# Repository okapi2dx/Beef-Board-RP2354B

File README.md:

# Beef Board RP2354B

Beef Board RP2354B の基板設計、ファームウェア、Windows 用 Configurator をまとめたプロジェクトです。Configurator は、RP2354B と従来の AT90USB1286 の2種類のマイコンを搭載した基板に対応します。

## 開発とソースコードの由来

基板、ファームウェア、Configurator の設計・実装・デバッグ・文書作成に AI を活用しています。仕様と設計の採用判断はプロジェクト管理者が行います。実機での確認状況は各ファームウェアの README に記載しています。

Configurator は [HWXLR8/beef-board](https://github.com/HWXLR8/beef-board) を基にした Beef Board ソフトウェアのフォーク／派生コードを出発点として、RP2354B 対応を加えています。

## Configurator

RP2354B・AT90USB1286に対応するWindowsアプリです。入力、LED、キー割り当てを設定し、モニターと波形で動作を確認できます。

[V1.00リリース](https://github.com/okapi2dx/Beef-Board-RP2354B/releases/tag/V1.00)から最新のアプリと基板用ファームを取得し、USB接続後に **「接続」** を押してください。設定は基板へ自動反映され、各項目の **「?」** で説明を確認できます。

以下は現在のアプリを日本語・ダークモードで表示した例です。画像内の入力・数値は説明用のサンプルです。

### 入力設定

入力モードを **ジョイスティック / キーボード** から選び、ターンテーブルの回転方向やアナログ / デジタル入力を設定します。下部の **X軸** で回転による入力を確認できます。

- **デッドゾーン：0～50カウント。** 小さな回転を無視する範囲です。0で無効になります。
- **感度：0.000～2.000。** 1.000が基準、0.500で半分、2.000で2倍の距離を進みます。0で入力無効、初期値は1.000です。
- **保持時間：** デジタル入力が途切れる場合に調整します。アナログ入力にはジョイスティックモードを使用してください。

### LED・RGB設定

**「ボタンLED設定」** では、ボタンの明るさ・フェードアウト時間・点灯反転を調整します。**「RGB LED設定」** では、ターンテーブルとセンターバーの色・発光効果を設定します。

- **連動：** ターンテーブルとセンターバーを同じ色・発光効果にできます。
- **変化速度：** 回転・シフト・動くレインボー・呼吸の速度を1～5で調整します。自動で色が変わる効果では、色選択がグレーアウトします。
- **LED数：** 接続したLED数に合わせて各0～255で設定します。初期値はターンテーブル24個、センターバー16個。0でそのLED出力を無効にします。
- **旧PHOENIXWAN：** RP2354BではUART接続によるLED制御に対応します。

| ボタンLED設定 | RGB LED設定 |
|---|---|
|  |  |

### コントローラーモニター

ボタンの入力、X軸、割り当て先とLEDの光り方を確認できます。**1P / 2P** で配置を切り替え、デジタル入力では回転方向を **B13 / B14** の点灯で表示します。

### チャタリングテスト

**B1～B7の波形と入力ログ** を見ながら、押下時・解放時の抑制を各 **0.0～16.0ms** で調整できます。一括設定と自動設定にも対応します。

**「抑制前 / 抑制後」** で、元の入力と現在の設定を適用した波形を比較します。ログを選んで **「詳細」** を押すと、そのボタンの50ms区間を拡大します。2つのエッジを選ぶと、間の押下・解放時間を測定できます。

### キー割り当て・ファームウェア更新

**「キー割り当て」** で、ボタンの割り当て先やキーボード入力のキーを変更できます。**「ファームウェア」** から更新方法を確認してください。AT90USB1286はHEXをアプリから書き込み、RP2354BはUF2をBOOTSELのUSBドライブへコピーします。

ライト / ダークと日本語 / Englishを切り替えられます。詳しい手順は [ConfiguratorのREADME](configurator/README.md)、[ファームウェアのREADME](firmware/README.md) を参照してください。

## 旧PHOENIXWAN UART

RP2354B基板のUART端子は、**旧PHOENIXWANのターンテーブルリングとセンターバーLEDを接続して制御する用途**です。ターンテーブルリングはJ42、センターバーはJ43に接続し、ConfiguratorのLED設定に合わせて制御します。このUART機能はAT90USB1286基板にはありません。

UARTプロトコルで設定できる色や発光パターンには制限があります。対応する制御内容と接続上の注意は [`firmware/README.md`](firmware/README.md) を参照してください。旧PHOENIXWAN実機での接続確認は未実施です。

## 電源選択（J2）

J2「POWER SELECT」のショート位置で、USBケーブル1本または2本の使い方を選べます。

| 使い方 | J2の設定 | 接続方法 |
|---|---|---|
| USBケーブル1本 | 1–2を短絡 | メインUSB端子に接続。基板本体とすべてのLEDに給電 |
| USBケーブル2本 | 2–3を短絡 | メインUSB端子で基板本体とボタンLEDに給電し、もう一方のUSB端子でターンテーブルとセンターバーのLEDに給電 |

J2には2.54 mmピッチの3ピンヘッダとショートピンを取り付けます。基板の印字「1・2・3」を確認し、ショートピンは1–2または2–3のどちらか一方だけに取り付けてください。

## 基板の接続案内

端子の位置と用途をまとめた接続案内図です。J番号で接続先を確認できます。

[接続案内図を拡大する](docs/wiring/connection-guide.png) · [SVG版](docs/wiring/connection-guide.svg)

キー割り当てを変更した場合は、設定した出力になります。

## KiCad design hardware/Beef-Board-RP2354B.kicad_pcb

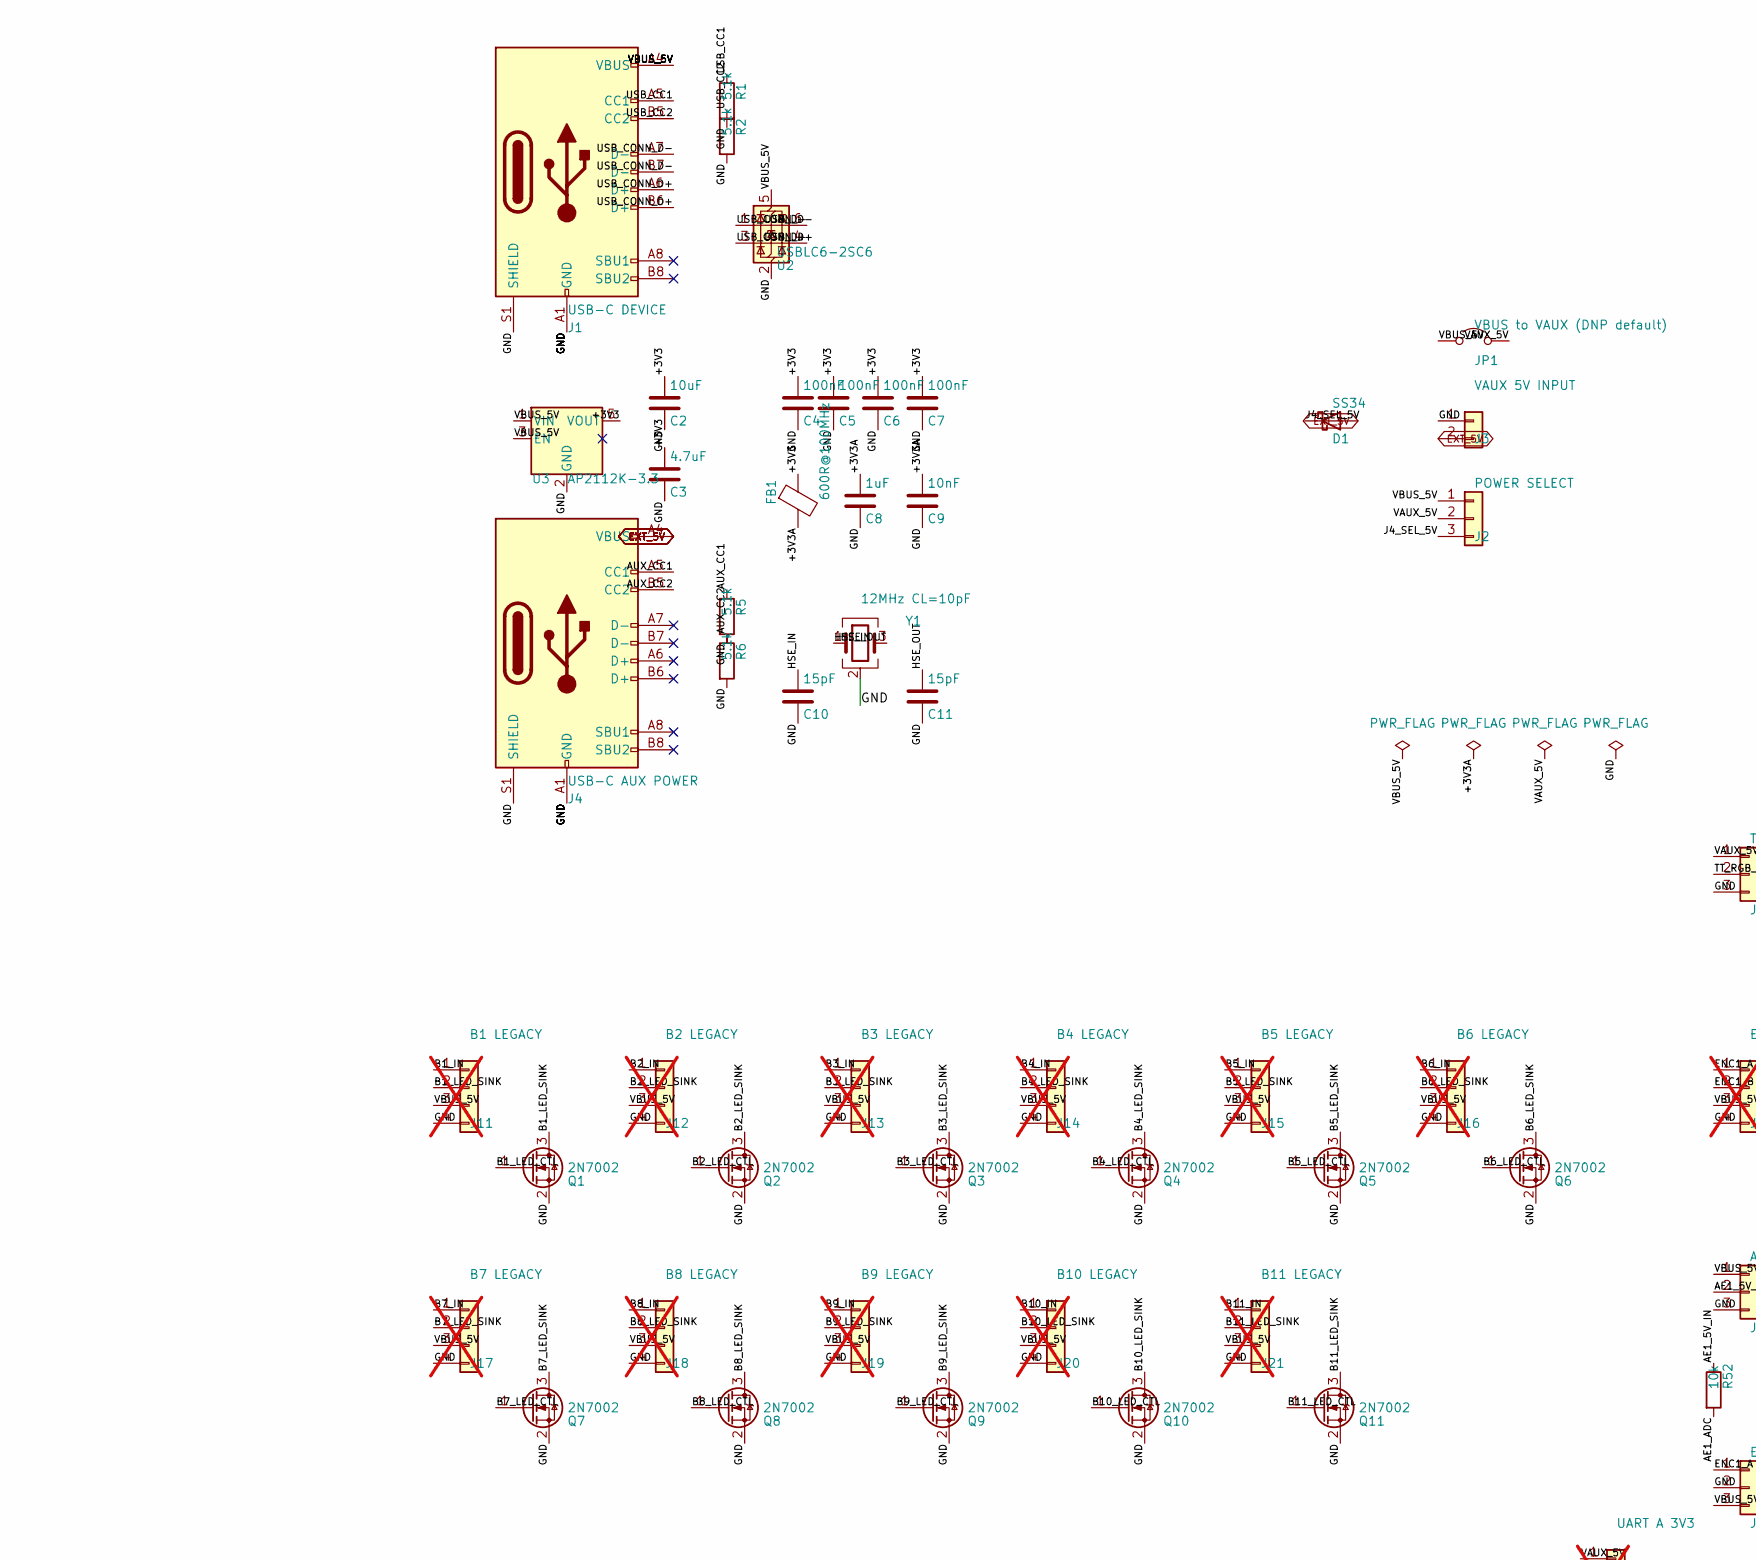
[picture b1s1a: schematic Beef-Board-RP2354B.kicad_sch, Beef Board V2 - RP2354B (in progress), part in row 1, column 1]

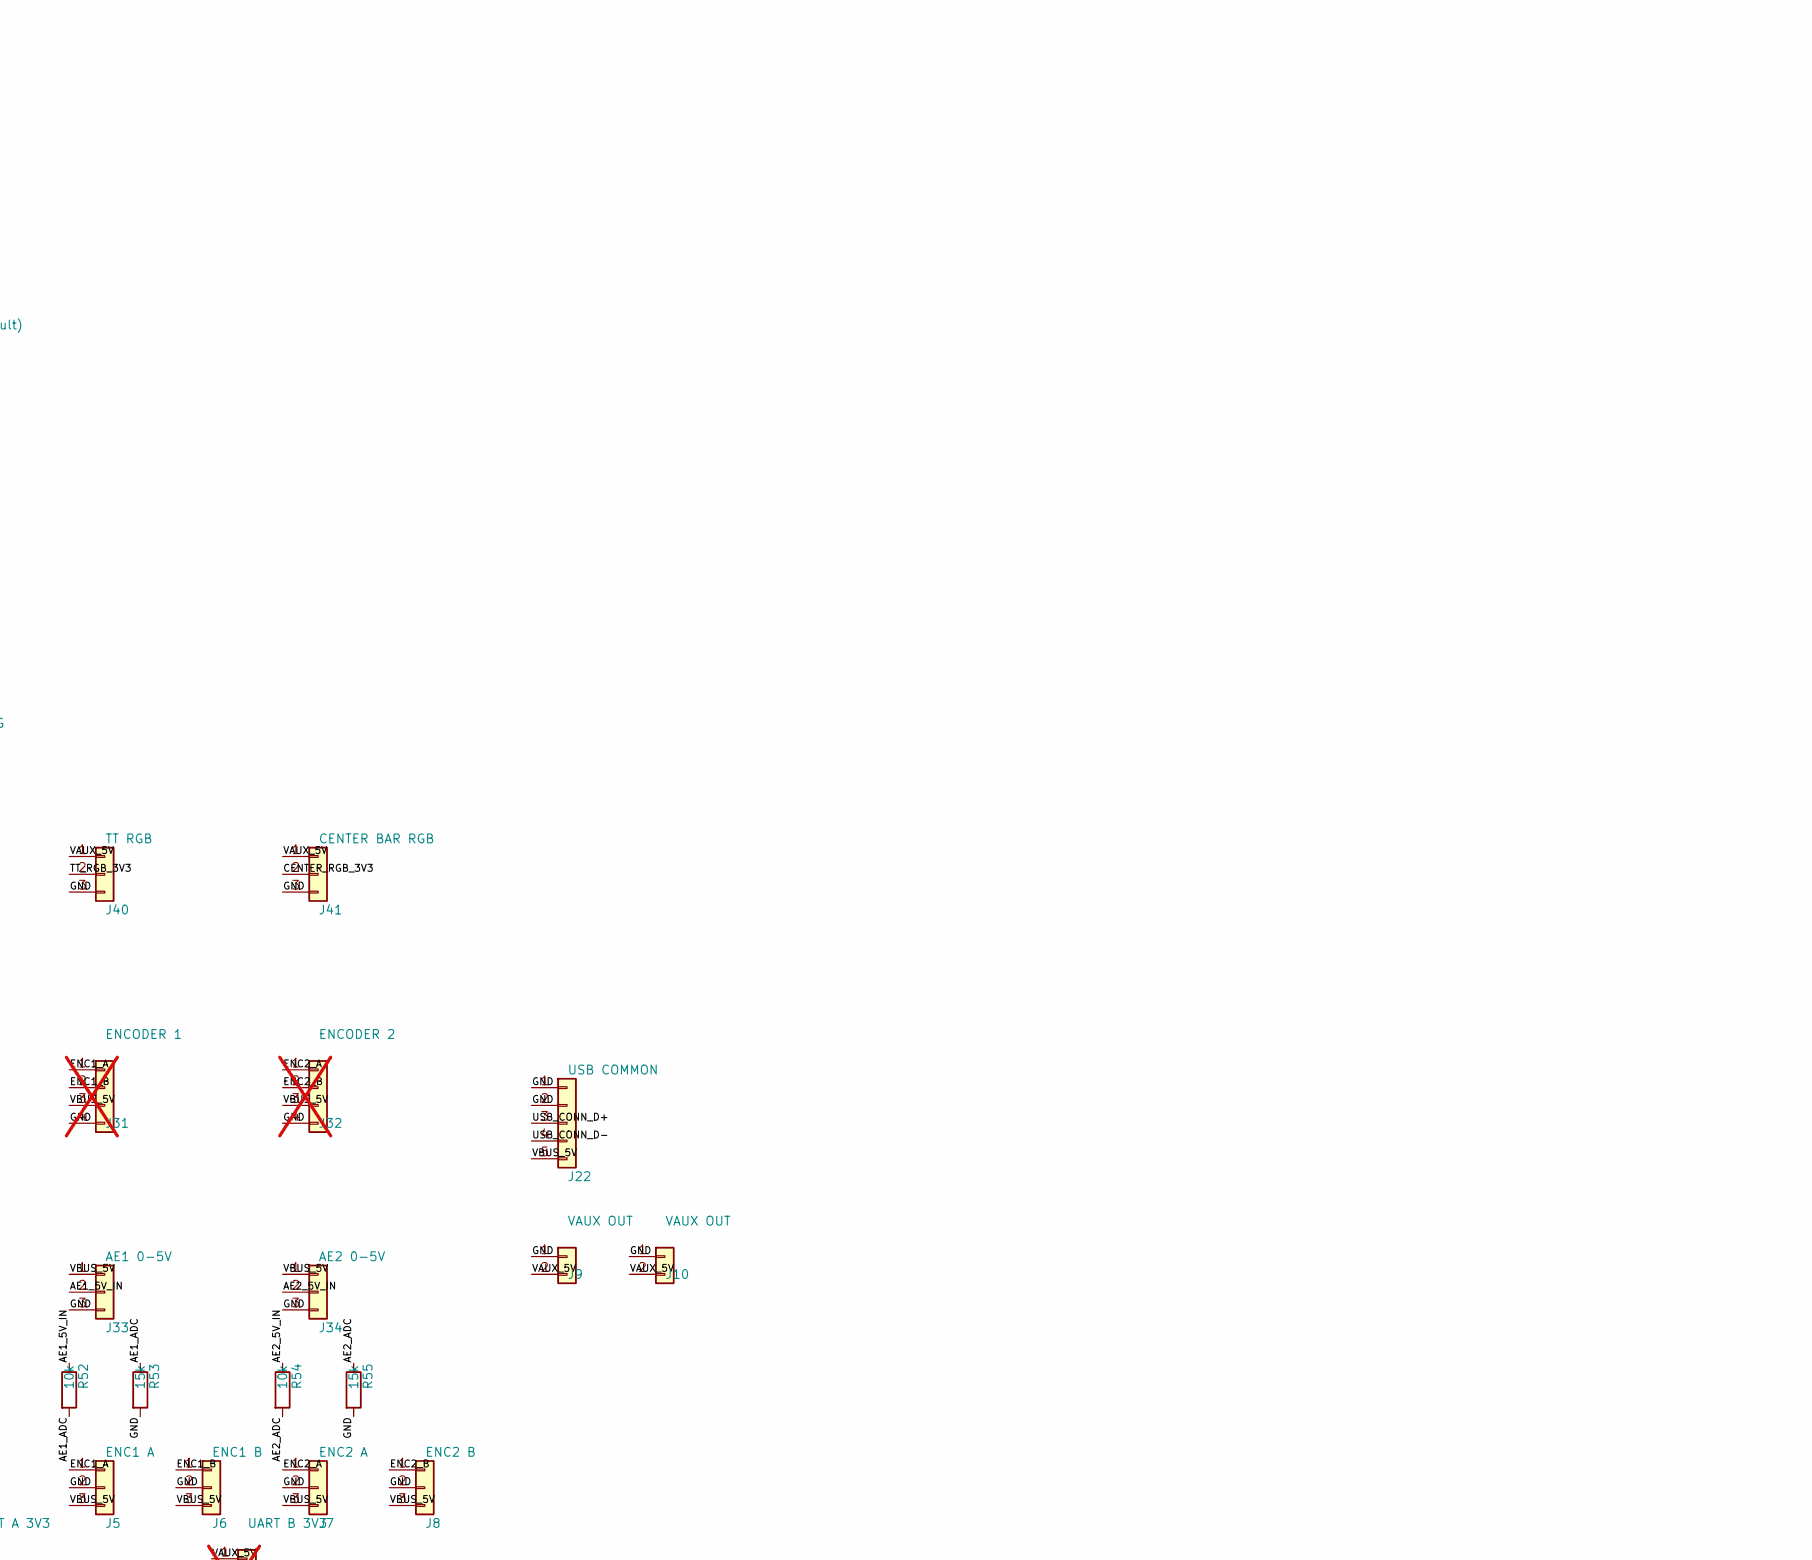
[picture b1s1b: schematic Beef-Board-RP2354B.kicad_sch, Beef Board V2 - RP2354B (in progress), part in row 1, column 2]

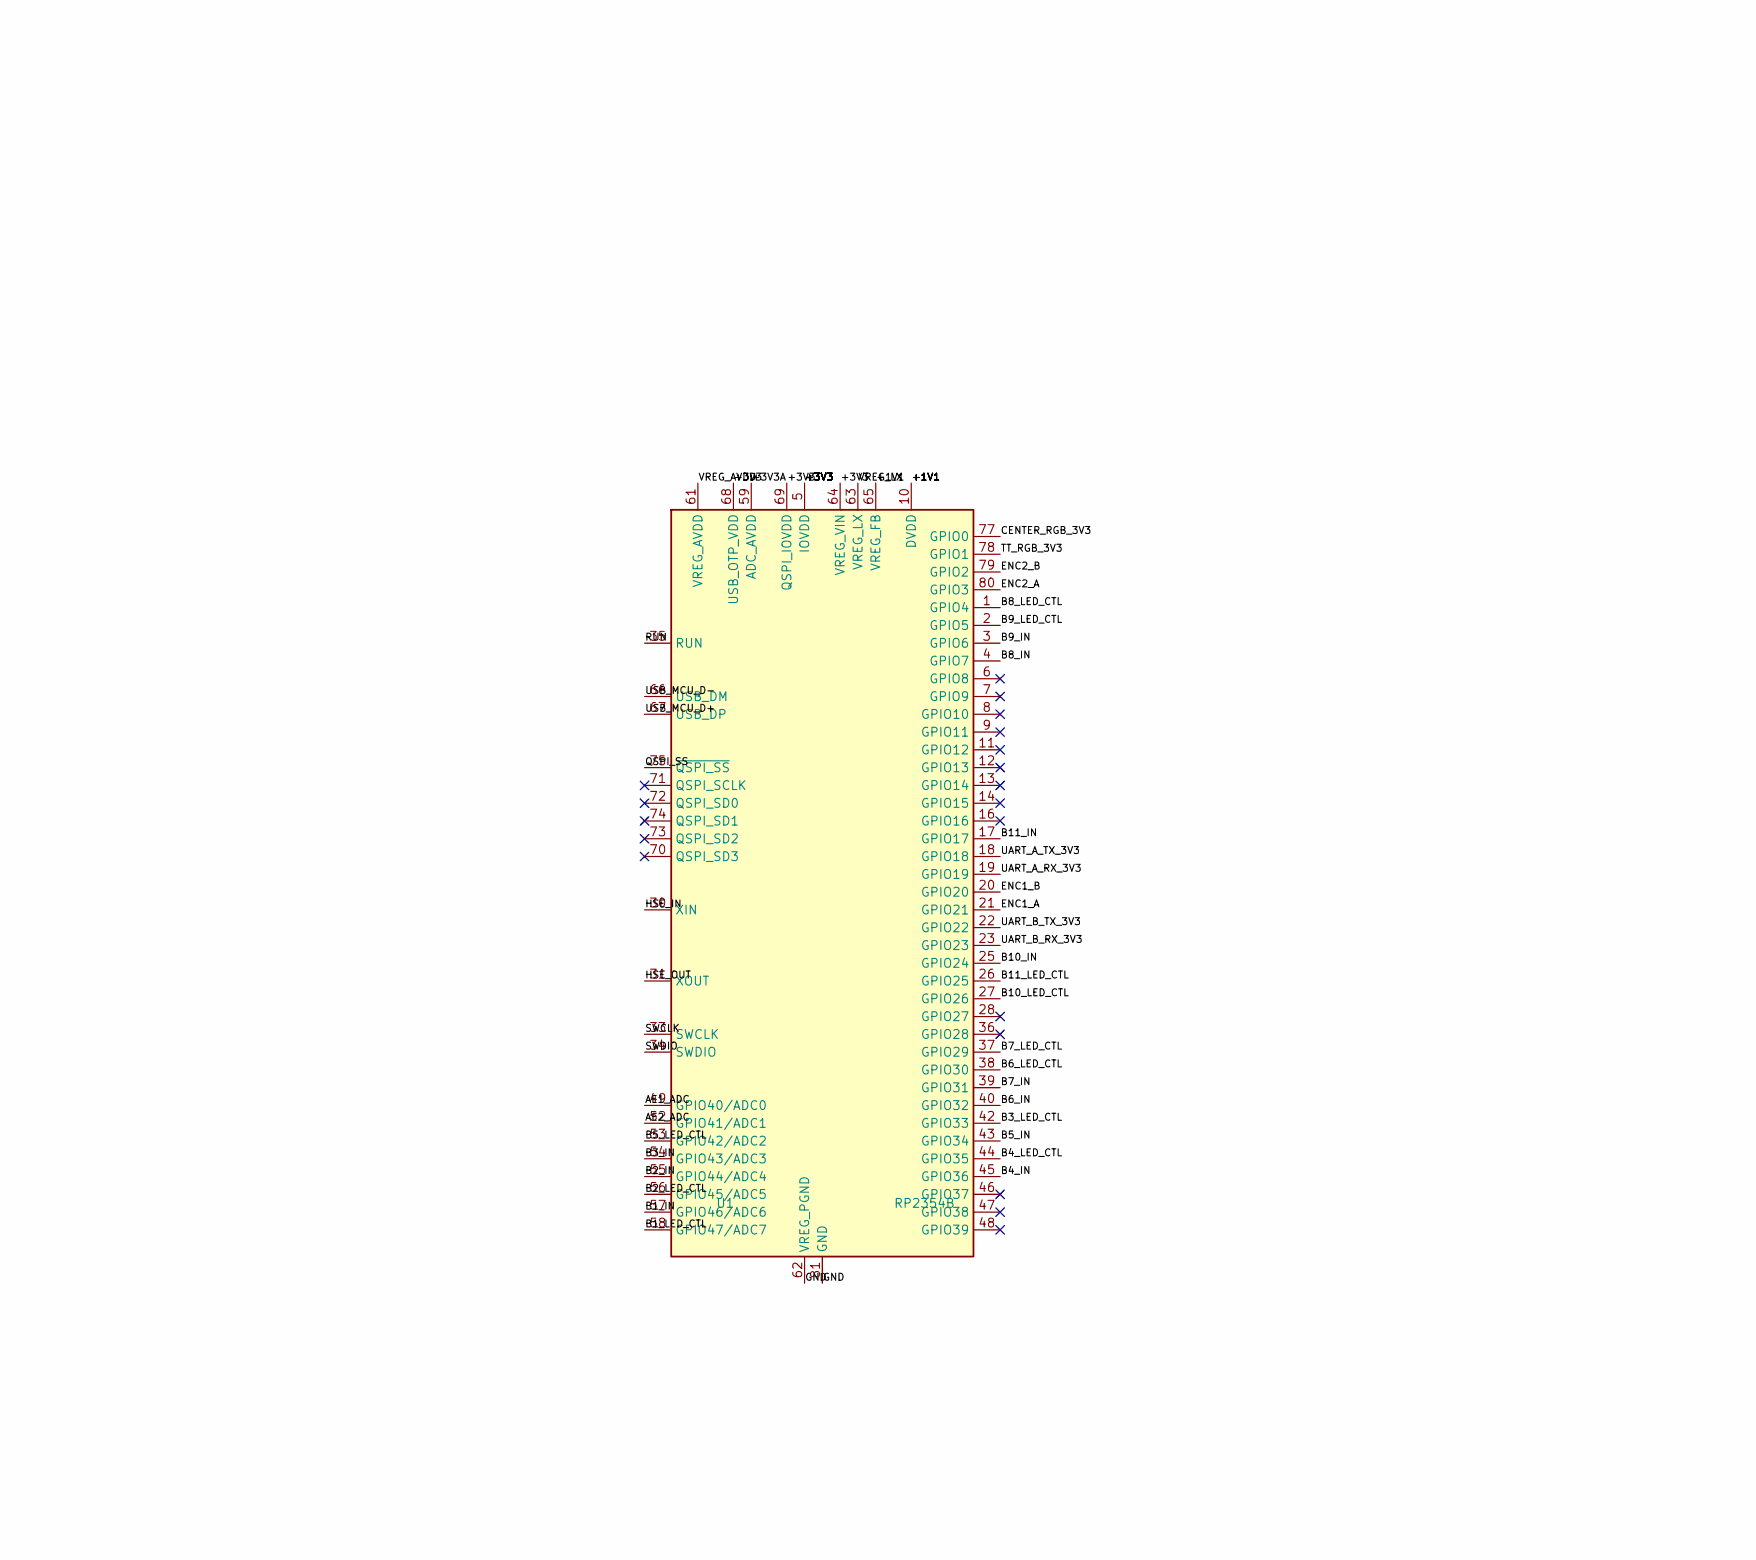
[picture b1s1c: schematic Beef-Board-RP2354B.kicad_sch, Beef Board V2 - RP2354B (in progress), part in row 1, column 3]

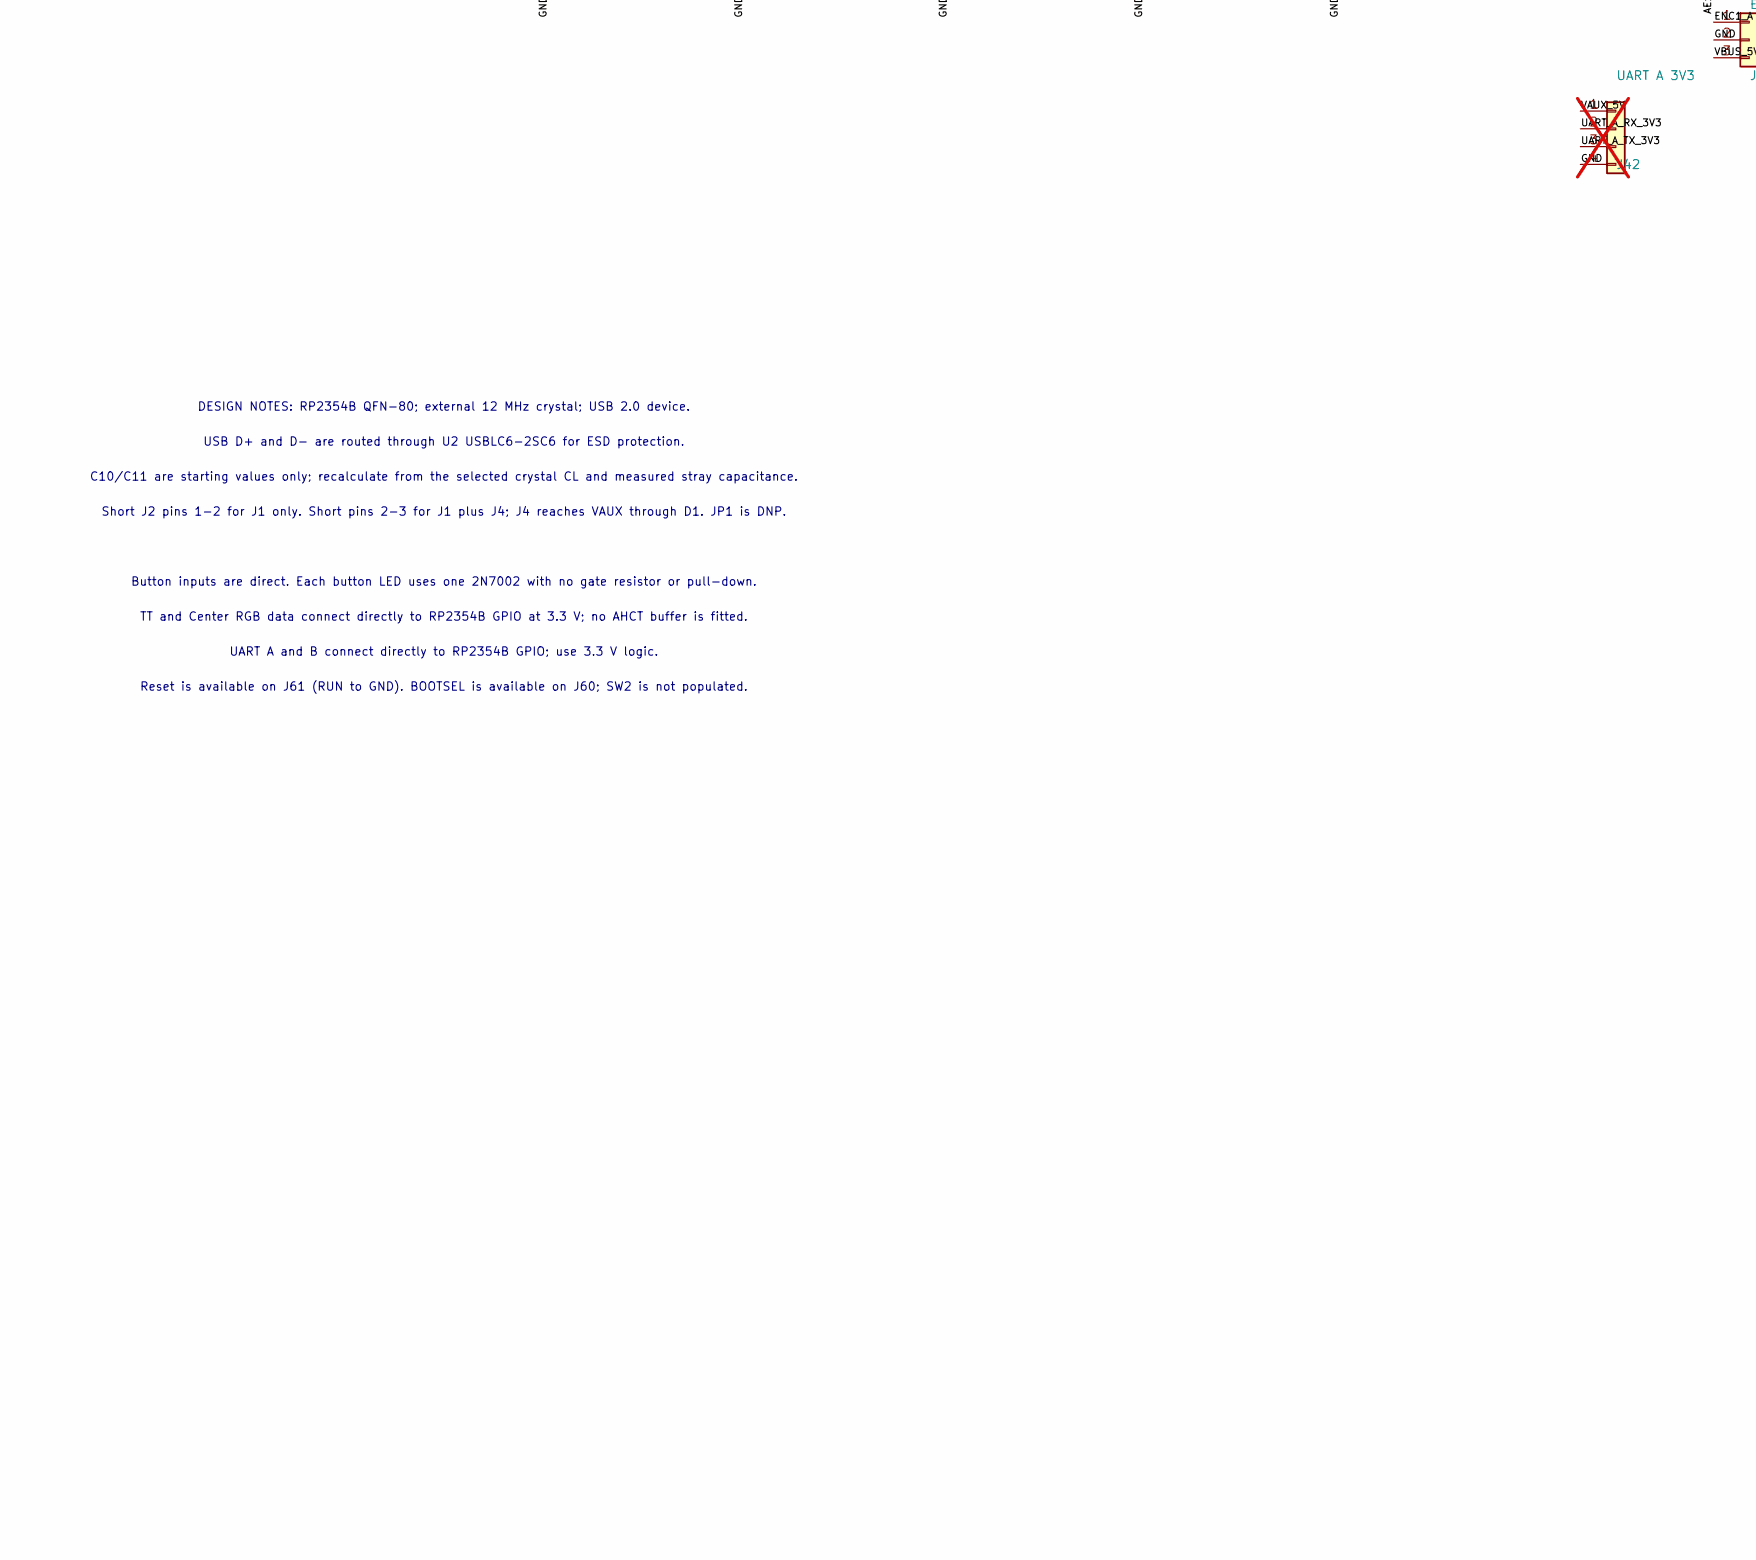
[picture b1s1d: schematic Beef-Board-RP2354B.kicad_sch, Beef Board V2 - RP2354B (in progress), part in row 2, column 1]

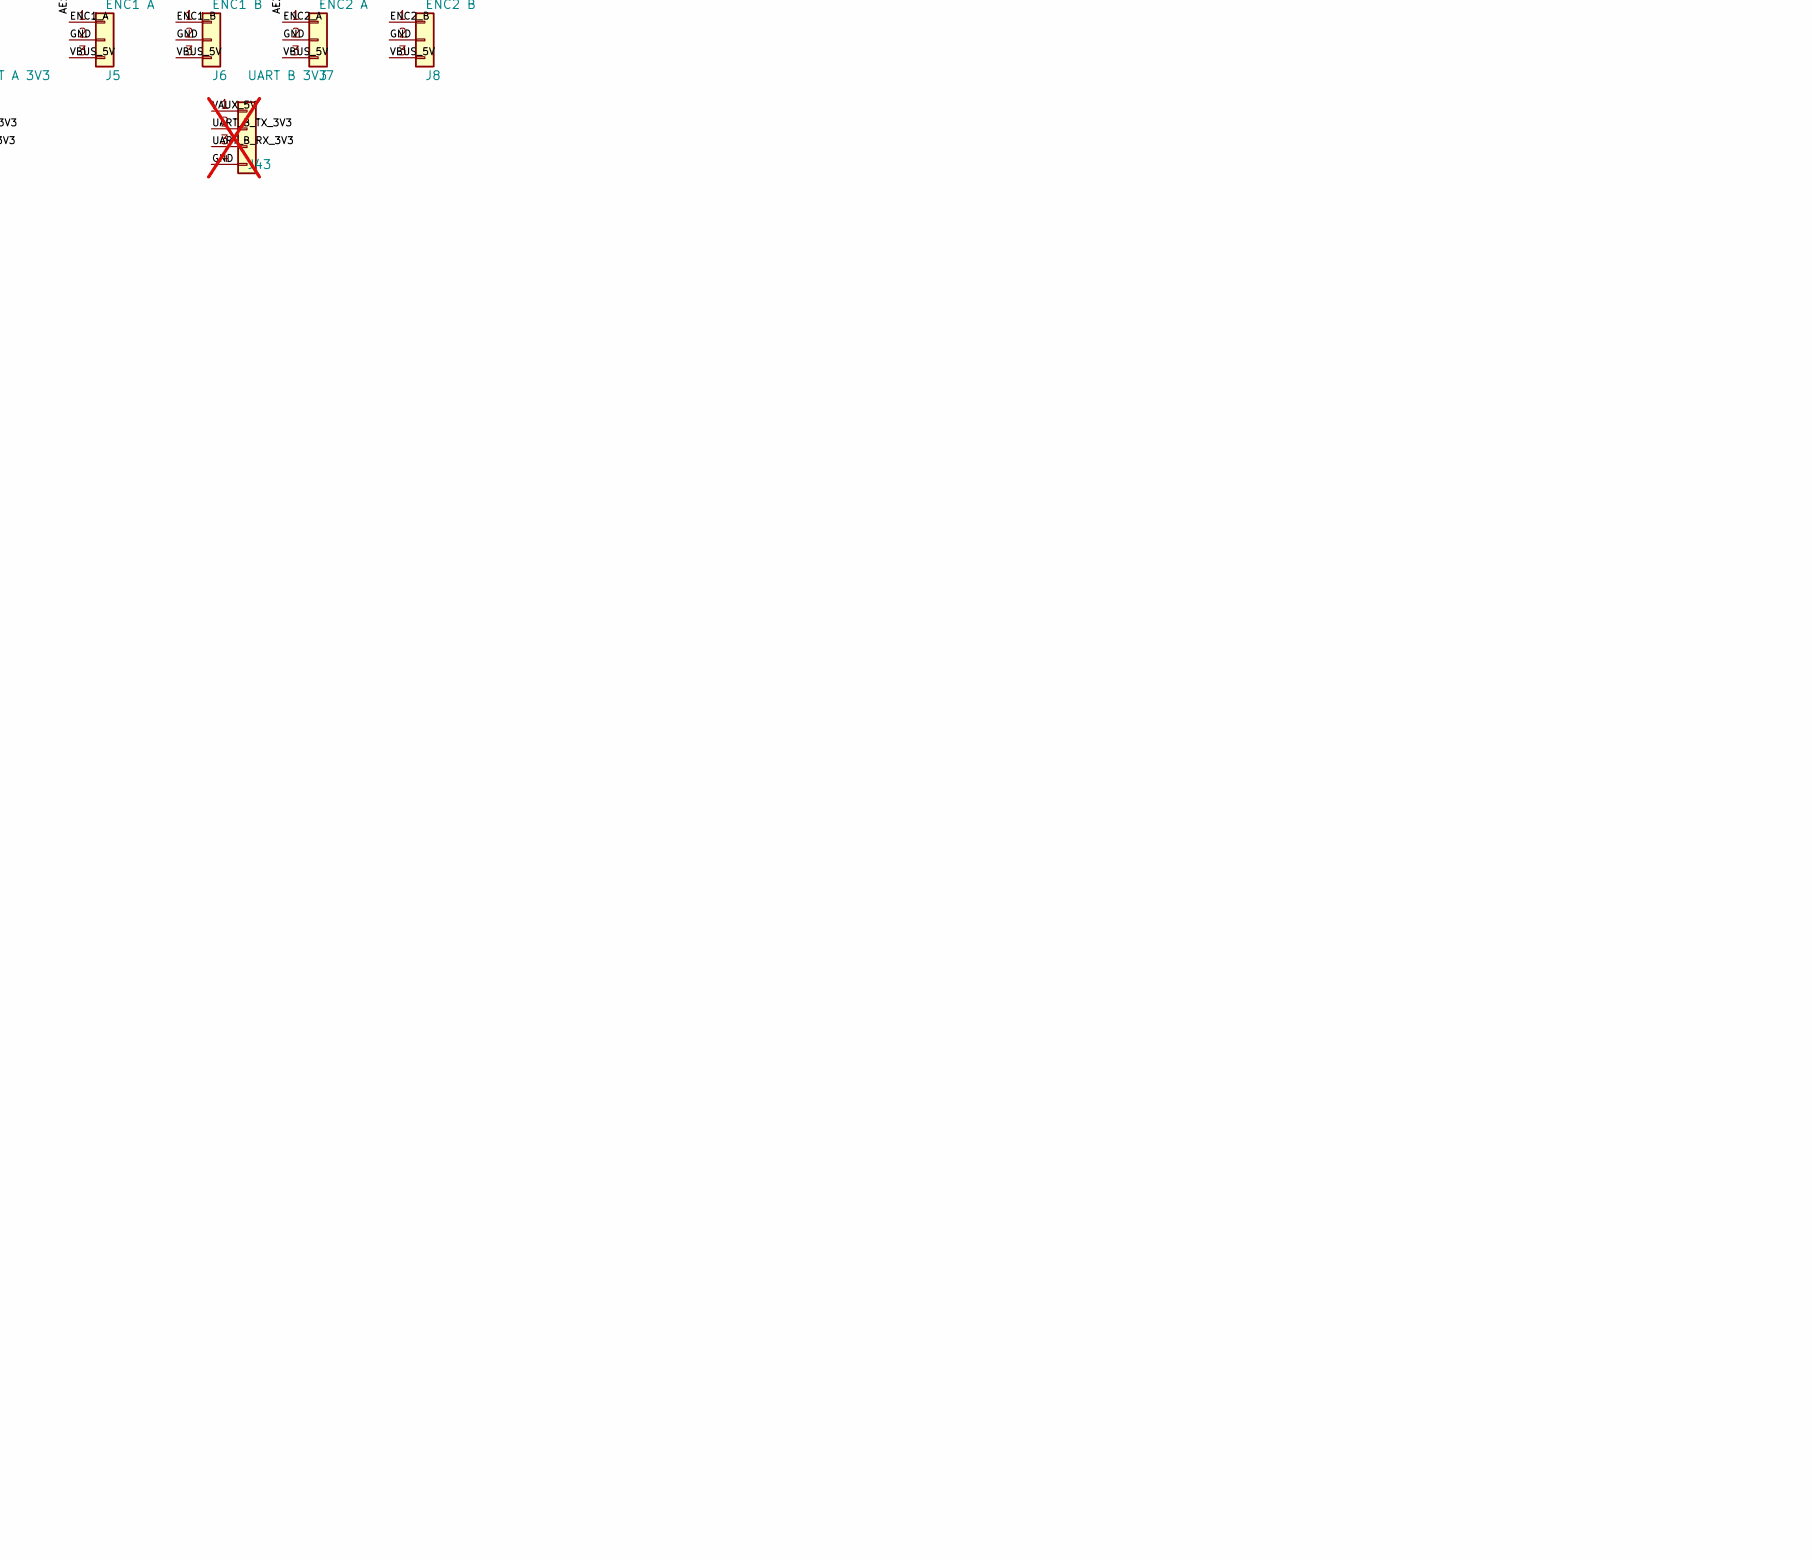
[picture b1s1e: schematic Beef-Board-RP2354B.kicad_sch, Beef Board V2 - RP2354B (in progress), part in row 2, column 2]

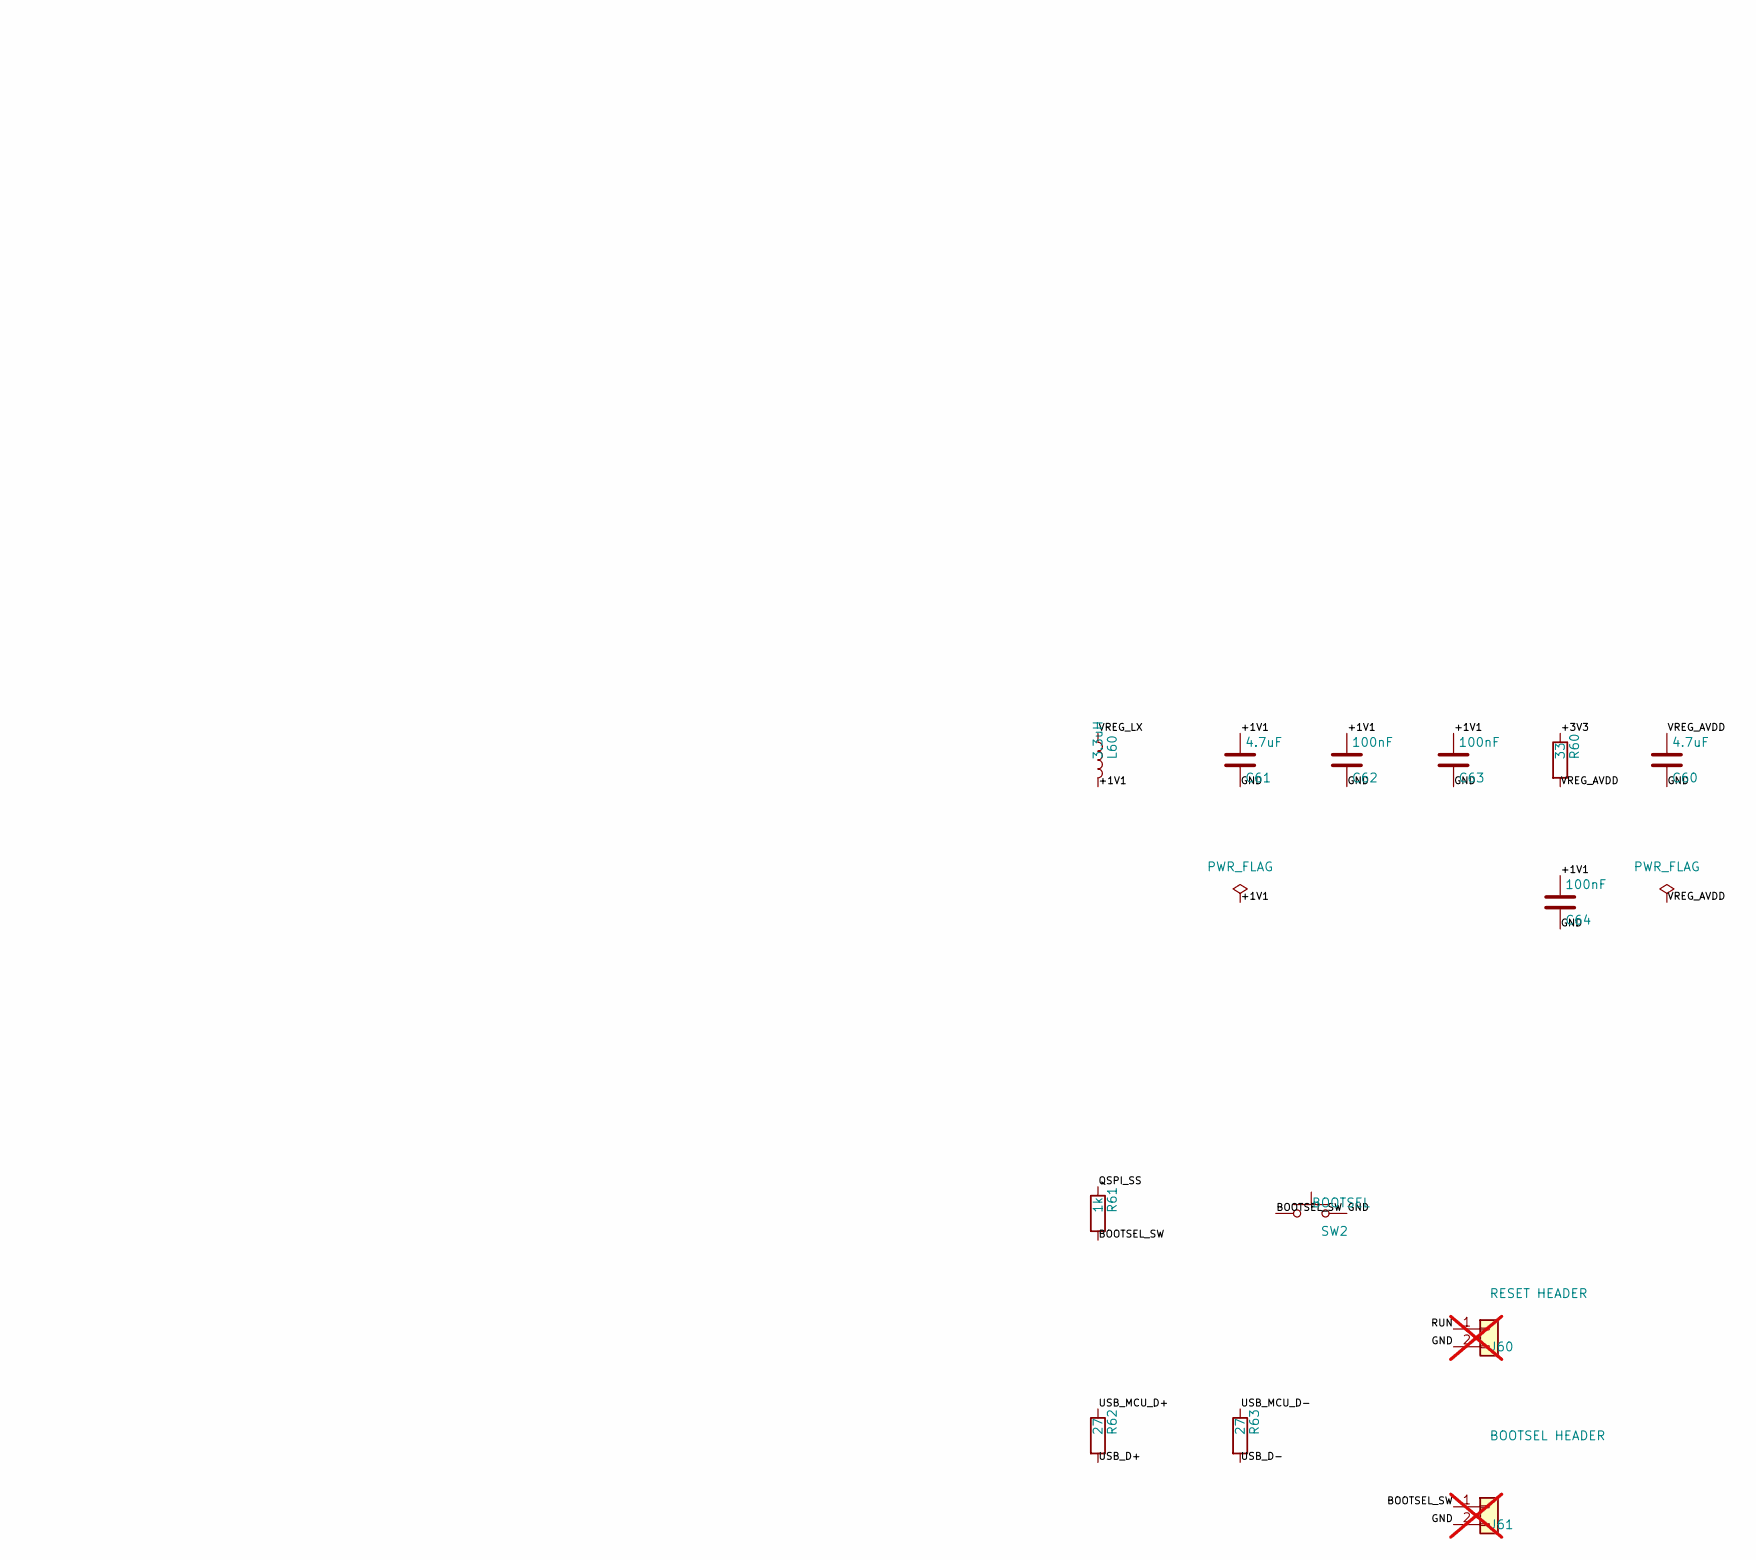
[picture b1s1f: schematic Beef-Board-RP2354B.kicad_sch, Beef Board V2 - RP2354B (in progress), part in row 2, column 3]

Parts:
C2: 10uF; C_0805_2012Metric
C3: 4.7uF; C_0805_2012Metric
C4, C5, C6, C7: 100nF; C_0603_1608Metric
C8: 1uF; C_0603_1608Metric
C9: 10nF; C_0603_1608Metric
C10, C11: 15pF; C_0603_1608Metric
C60, C61: 4.7uF; C_0402_1005Metric
C62, C63, C64: 100nF; C_0402_1005Metric
D1: SS34; D_SMA
FB1: 600R@100MHz; L_0603_1608Metric_Pad1.05x0.95mm_HandSolder
J1: USB-C DEVICE; USB-C-TH_G-SWITCH_GT-USB-7038X_1
J2: POWER SELECT; PinHeader_1x03_P2.54mm_Vertical
J3: VAUX 5V INPUT; JST_PH_B2B-PH-K_1x02_P2.00mm_Vertical
J4: USB-C AUX POWER; USB-C-TH_G-SWITCH_GT-USB-7038X_1
J5: ENC1 A; JST_XH_B3B-XH-A_1x03_P2.50mm_Vertical
J6: ENC1 B; JST_XH_B3B-XH-A_1x03_P2.50mm_Vertical
J7: ENC2 A; JST_XH_B3B-XH-A_1x03_P2.50mm_Vertical
J8: ENC2 B; JST_XH_B3B-XH-A_1x03_P2.50mm_Vertical
J9, J10: VAUX OUT; JST_XH_B2B-XH-A_1x02_P2.50mm_Vertical
J11: B1 LEGACY; JST_XH_B4B-XH-A_1x04_P2.50mm_Vertical; not fitted
J12: B2 LEGACY; JST_XH_B4B-XH-A_1x04_P2.50mm_Vertical; not fitted
J13: B3 LEGACY; JST_XH_B4B-XH-A_1x04_P2.50mm_Vertical; not fitted
J14: B4 LEGACY; JST_XH_B4B-XH-A_1x04_P2.50mm_Vertical; not fitted
J15: B5 LEGACY; JST_XH_B4B-XH-A_1x04_P2.50mm_Vertical; not fitted
J16: B6 LEGACY; JST_XH_B4B-XH-A_1x04_P2.50mm_Vertical; not fitted
J17: B7 LEGACY; JST_XH_B4B-XH-A_1x04_P2.50mm_Vertical; not fitted
J18: B8 LEGACY; JST_XH_B4B-XH-A_1x04_P2.50mm_Vertical; not fitted
J19: B9 LEGACY; JST_XH_B4B-XH-A_1x04_P2.50mm_Vertical; not fitted
J20: B10 LEGACY; JST_XH_B4B-XH-A_1x04_P2.50mm_Vertical; not fitted
J21: B11 LEGACY; JST_XH_B4B-XH-A_1x04_P2.50mm_Vertical; not fitted
J22: USB COMMON; JST_XH_B5B-XH-A_1x05_P2.50mm_Vertical
J31: ENCODER 1; JST_XH_B4B-XH-A_1x04_P2.50mm_Vertical; not fitted
J32: ENCODER 2; JST_XH_B4B-XH-A_1x04_P2.50mm_Vertical; not fitted
J33: AE1 0-5V; JST_PH_B3B-PH-K_1x03_P2.00mm_Vertical
J34: AE2 0-5V; JST_PH_B3B-PH-K_1x03_P2.00mm_Vertical
J40: TT RGB; JST_XH_B3B-XH-A_1x03_P2.50mm_Vertical
J41: CENTER BAR RGB; JST_XH_B3B-XH-A_1x03_P2.50mm_Vertical
J42: UART A 3V3; JST_XH_B4B-XH-A_1x04_P2.50mm_Vertical; not fitted
J43: UART B 3V3; JST_XH_B4B-XH-A_1x04_P2.50mm_Vertical; not fitted
J60: RESET HEADER; PinHeader_1x02_P2.54mm_Vertical; not fitted
J61: BOOTSEL HEADER; PinHeader_1x02_P2.54mm_Vertical; not fitted
JP1: VBUS to VAUX (DNP default); SolderJumper-2_P1.3mm_Open_Pad1.0x1.5mm
L60: 3.3uH; RP2354B_VREG_L_3u3
Q1, Q2, Q3, Q4, Q5, Q6, Q7, Q8, Q9, Q10, Q11: 2N7002; SOT-23
R1, R2, R5, R6: 5.1k; R_0603_1608Metric
R52, R54: 10k; R_0603_1608Metric
R53, R55: 15k; R_0603_1608Metric
R60: 33; R_0603_1608Metric
R61: 1k; R_0603_1608Metric
R62, R63: 27; R_0402_1005Metric
SW2: BOOTSEL; SW_SPST_TL3342
U1: RP2354B; QFN-80-1EP_10x10mm_P0.4mm_EP3.4x3.4mm
U2: USBLC6-2SC6; SOT-23-6
U3: AP2112K-3.3; SOT-23-5
Y1: 12MHz CL=10pF; Crystal_SMD_3225-4Pin_3.2x2.5mm

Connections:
/+1V1: C61.1, C62.1, C63.1, C64.1, L60.2, U1.10 (DVDD), U1.32 (DVDD), U1.51 (DVDD), U1.65 (VREG_FB)
/+3V3: C2.1, C3.1, C4.1, C5.1, C6.1, C7.1, FB1.1, R60.1, U1.5 (IOVDD), U1.15 (IOVDD), U1.24 (IOVDD), U1.29 (IOVDD), U1.41 (IOVDD), U1.50 (IOVDD), U1.60 (IOVDD), U1.64 (VREG_VIN), U1.68 (USB_OTP_VDD), U1.69 (QSPI_IOVDD), U1.76 (IOVDD), U3.5 (VOUT)
/+3V3A: C8.1, C9.1, FB1.2, U1.59 (ADC_AVDD)
/AE1_5V_IN: J33.2, R52.1
/AE1_ADC: R52.2, R53.1, U1.49 (GPIO40/ADC0)
/AE2_5V_IN: J34.2, R54.1
/AE2_ADC: R54.2, R55.1, U1.52 (GPIO41/ADC1)
/AUX_CC1: J4.A5 (CC1), R5.1
/AUX_CC2: J4.B5 (CC2), R6.1
/B1_IN: J11.1, U1.57 (GPIO46/ADC6)
/B1_LED_CTL: Q1.1 (G), U1.58 (GPIO47/ADC7)
/B1_LED_SINK: J11.2, Q1.3 (D)
/B2_IN: J12.1, U1.55 (GPIO44/ADC4)
/B2_LED_CTL: Q2.1 (G), U1.56 (GPIO45/ADC5)
/B2_LED_SINK: J12.2, Q2.3 (D)
/B3_IN: J13.1, U1.54 (GPIO43/ADC3)
/B3_LED_CTL: Q3.1 (G), U1.42 (GPIO33)
/B3_LED_SINK: J13.2, Q3.3 (D)
/B4_IN: J14.1, U1.45 (GPIO36)
/B4_LED_CTL: Q4.1 (G), U1.44 (GPIO35)
/B4_LED_SINK: J14.2, Q4.3 (D)
/B5_IN: J15.1, U1.43 (GPIO34)
/B5_LED_CTL: Q5.1 (G), U1.53 (GPIO42/ADC2)
/B5_LED_SINK: J15.2, Q5.3 (D)
/B6_IN: J16.1, U1.40 (GPIO32)
/B6_LED_CTL: Q6.1 (G), U1.38 (GPIO30)
/B6_LED_SINK: J16.2, Q6.3 (D)
/B7_IN: J17.1, U1.39 (GPIO31)
/B7_LED_CTL: Q7.1 (G), U1.37 (GPIO29)
/B7_LED_SINK: J17.2, Q7.3 (D)
/B8_IN: J18.1, U1.4 (GPIO7)
/B8_LED_CTL: Q8.1 (G), U1.1 (GPIO4)
/B8_LED_SINK: J18.2, Q8.3 (D)
/B9_IN: J19.1, U1.3 (GPIO6)
/B9_LED_CTL: Q9.1 (G), U1.2 (GPIO5)
/B9_LED_SINK: J19.2, Q9.3 (D)
/B10_IN: J20.1, U1.25 (GPIO24)
/B10_LED_CTL: Q10.1 (G), U1.27 (GPIO26)
/B10_LED_SINK: J20.2, Q10.3 (D)
/B11_IN: J21.1, U1.17 (GPIO17)
/B11_LED_CTL: Q11.1 (G), U1.26 (GPIO25)
/B11_LED_SINK: J21.2, Q11.3 (D)
/BOOTSEL_SW: J61.1, R61.2, SW2.1
/CENTER_RGB_3V3: J41.2, U1.77 (GPIO0)
/ENC1_A: J5.1, J31.1, U1.21 (GPIO21)
/ENC1_B: J6.1, J31.2, U1.20 (GPIO20)
/ENC2_A: J7.1, J32.1, U1.80 (GPIO3)
/ENC2_B: J8.1, J32.2, U1.79 (GPIO2)
/GND: C2.2, C3.2, C4.2, C5.2, C6.2, C7.2, C8.2, C9.2, C10.2, C11.2, C60.2, C61.2, C62.2, C63.2, C64.2, J1.13, J1.A1 (GND), J1.A1B12, J1.A12 (GND), J1.A12B1, J1.B1 (GND), J1.B12 (GND), J1.S1 (SHIELD), J3.1, J4.13, J4.A1 (GND), J4.A1B12, J4.A12 (GND), J4.A12B1, J4.B1 (GND), J4.B12 (GND), J4.S1 (SHIELD), J5.2, J6.2, J7.2, J8.2, J9.1, J10.1, J11.4, J12.4, J13.4, J14.4, J15.4, J16.4, J17.4, J18.4, J19.4, J20.4, J21.4, J22.1, J22.2, J31.4, J32.4, J33.3, J34.3, J40.3, J41.3, J42.4, J43.4, J60.2, J61.2, Q1.2 (S), Q2.2 (S), Q3.2 (S), Q4.2 (S), Q5.2 (S), Q6.2 (S), Q7.2 (S), Q8.2 (S), Q9.2 (S), Q10.2 (S), Q11.2 (S), R1.2, R2.2, R5.2, R6.2, R53.2, R55.2, SW2.2, U1.62 (VREG_PGND), U1.81 (GND), U2.2 (GND), U3.2 (GND), Y1.2 (G), Y1.4 (G)
/HSE_IN: C10.1, U1.30 (XIN), Y1.1
/HSE_OUT: C11.1, U1.31 (XOUT), Y1.3
/J4_SEL_5V: D1.1 (K), J2.3
/QSPI_SS: R61.1, U1.75 (~QSPI_SS)
/RUN: J60.1, U1.35 (RUN)
/SWCLK: U1.33 (SWCLK)
/SWDIO: U1.34 (SWDIO)
/TT_RGB_3V3: J40.2, U1.78 (GPIO1)
/UART_A_RX_3V3: J42.2, U1.19 (GPIO19)
/UART_A_TX_3V3: J42.3, U1.18 (GPIO18)
/UART_B_RX_3V3: J43.3, U1.23 (GPIO23)
/UART_B_TX_3V3: J43.2, U1.22 (GPIO22)
/USB_CC1: J1.A5 (CC1), R1.1
/USB_CC2: J1.B5 (CC2), R2.1
/USB_CONN_D+: J1.A6 (D+), J1.B6 (D+), J22.3, U2.3 (I/O2)
/USB_CONN_D-: J1.A7 (D-), J1.B7 (D-), J22.4, U2.1 (I/O1)
/USB_D+: R62.2, U2.4 (I/O2)
/USB_D-: R63.2, U2.6 (I/O1)
/USB_MCU_D+: R62.1, U1.67 (USB_DP)
/USB_MCU_D-: R63.1, U1.66 (USB_DM)
/VAUX_5V: J2.2, J9.2, J10.2, J40.1, J41.1, J42.1, J43.1, JP1.2 (B)
/VBUS_5V: J1.A4 (VBUS), J1.A4B9, J1.A9 (VBUS), J1.A9B4, J1.B4 (VBUS), J1.B9 (VBUS), J2.1, J5.3, J6.3, J7.3, J8.3, J11.3, J12.3, J13.3, J14.3, J15.3, J16.3, J17.3, J18.3, J19.3, J20.3, J21.3, J22.5, J31.3, J32.3, J33.1, J34.1, JP1.1 (A), U2.5 (VBUS), U3.1 (VIN), U3.3 (EN)
/VREG_AVDD: C60.1, R60.2, U1.61 (VREG_AVDD)
/VREG_LX: L60.1, U1.63 (VREG_LX)
EXT_5V: D1.2 (A), J3.2, J4.A4 (VBUS), J4.A4B9, J4.A9 (VBUS), J4.A9B4, J4.B4 (VBUS), J4.B9 (VBUS)

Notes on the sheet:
DESIGN NOTES: RP2354B QFN-80; external 12 MHz crystal; USB 2.0 device.
USB D+ and D- are routed through U2 USBLC6-2SC6 for ESD protection.
C10/C11 are starting values only; recalculate from the selected crystal CL and measured stray capacitance.
Short J2 pins 1-2 for J1 only. Short pins 2-3 for J1 plus J4; J4 reaches VAUX through D1. JP1 is DNP.
Button inputs are direct. Each button LED uses one 2N7002 with no gate resistor or pull-down.
TT and Center RGB data connect directly to RP2354B GPIO at 3.3 V; no AHCT buffer is fitted.
UART A and B connect directly to RP2354B GPIO; use 3.3 V logic.
Reset is available on J61 (RUN to GND). BOOTSEL is available on J60; SW2 is not populated.
